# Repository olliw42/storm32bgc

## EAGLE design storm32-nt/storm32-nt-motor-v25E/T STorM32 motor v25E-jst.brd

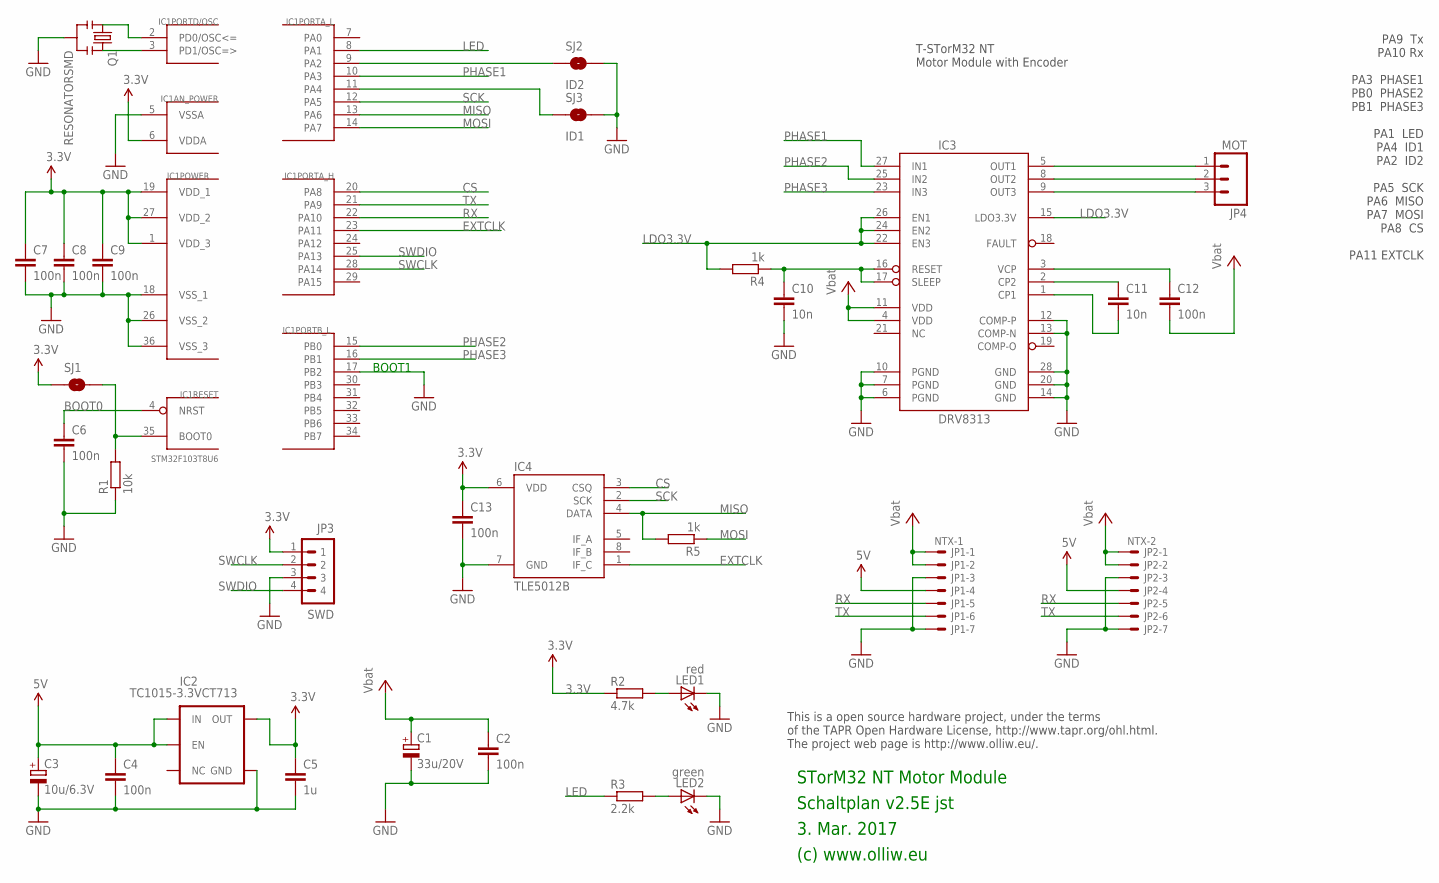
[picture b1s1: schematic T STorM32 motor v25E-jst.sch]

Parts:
C1: 33u/20V; SMC_C
C2, C4, C6, C7, C8, C9, C12, C13: 100n; C0603
C3: 10u/6.3V; SMC_B
C5: 1u; C0603
C10, C11: 10n; C0603
IC1: STM32F103T8U6; VFQFPN36
IC2: TC1015-3.3VCT713; SOT23-5
IC3: DRV8313; HTSSOP28
IC4: TLE5012B; SO08
JP1: NTX-1; SM07B-SRSS-TB
JP2: NTX-2; SM07B-SRSS-TB
JP3: SWD; 4X1_1P27_OCT_BILEX
JP4: MOT; 1X03
LED1: red; CHIPLED_0603
LED2: green; CHIPLED_0603
Q1: RESONATORSMD; RESONATOR-SMD
R1: 10k; R0603
R2: 4.7k; R0603
R3: 2.2k; R0603
R4, R5: 1k; R0603
SJ1: BOOT0; SJ_2S-NO
SJ2: ID2; SJ_2S-NO
SJ3: ID1; SJ_2S-NO

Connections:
3.3V: C5.1, C7.1, C8.1, C9.1, C13.1, IC1.1 (VDD_3), IC1.6 (VDDA), IC1.19 (VDD_1), IC1.27 (VDD_2), IC2.5 (OUT), IC4.6 (VDD), JP3.1, R2.1, SJ1.1
5V: C3.+, C4.1, IC2.1 (IN), IC2.3 (EN), JP1.4, JP2.4
CS: IC1.20 (PA8), IC4.3 (CSQ)
EXTCLK: IC1.23 (PA11), IC4.1 (IF_C)
GND: C1.-, C2.2, C3.-, C4.2, C5.2, C6.2, C7.2, C8.2, C9.2, C10.2, C13.2, IC1.5 (VSSA), IC1.17 (PB2), IC1.18 (VSS_1), IC1.26 (VSS_2), IC1.36 (VSS_3), IC2.2 (GND), IC3.6 (PGND), IC3.7 (PGND), IC3.10 (PGND), IC3.12 (COMP-P), IC3.13 (COMP-N), IC3.14 (GND), IC3.20 (GND), IC3.28 (GND), IC4.7 (GND), JP1.3, JP1.7, JP2.3, JP2.7, JP3.3, LED1.C, LED2.C, Q1.2, R1.1, SJ2.2, SJ3.2
LDO3.3V: IC3.15 (LDO3.3V), IC3.22 (EN3), IC3.24 (EN2), IC3.26 (EN1), R4.2
LED: IC1.8 (PA1), R3.1
MISO: IC1.13 (PA6), IC4.4 (DATA), R5.2
MOSI: IC1.14 (PA7), R5.1
unnamed: IC3.9 (OUT3), JP4.3
unnamed: IC1.9 (PA2), SJ2.1
unnamed: IC1.11 (PA4), SJ3.1
unnamed: C6.1, IC1.4 (NRST)
unnamed: IC1.35 (BOOT0), R1.2, SJ1.2
unnamed: IC1.2 (PD0/OSC<=), Q1.1
unnamed: IC1.3 (PD1/OSC=>), Q1.3
unnamed: LED1.A, R2.2
unnamed: LED2.A, R3.2
unnamed: IC3.8 (OUT2), JP4.2
unnamed: IC3.5 (OUT1), JP4.1
unnamed: C11.1, IC3.2 (CP2)
unnamed: C11.2, IC3.1 (CP1)
unnamed: C10.1, IC3.16 (RESET), IC3.17 (SLEEP), R4.1
unnamed: C12.1, IC3.3 (VCP)
PHASE1: IC1.10 (PA3), IC3.27 (IN1)
PHASE2: IC1.15 (PB0), IC3.25 (IN2)
PHASE3: IC1.16 (PB1), IC3.23 (IN3)
RX: IC1.22 (PA10), JP1.5, JP2.5
SCK: IC1.12 (PA5), IC4.2 (SCK)
SWCLK: IC1.28 (PA14), JP3.2
SWDIO: IC1.25 (PA13), JP3.4
TX: IC1.21 (PA9), JP1.6, JP2.6
VCC: C1.+, C2.1, C12.2, IC3.4 (VDD), IC3.11 (VDD), JP1.1, JP1.2, JP2.1, JP2.2

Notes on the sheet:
3. Mar. 2017
(c) www.olliw.eu
STorM32 NT Motor Module
Schaltplan v2.5E jst
This is a open source hardware project, under the terms of the TAPR Open Hardware License, http://www.tapr.org/ohl.html. The project web page is http://www.olliw.eu/.
T-STorM32 NT Motor Module with Encoder
BOOT1
PA9 Tx PA10 Rx PA3 PHASE1 PB0 PHASE2 PB1 PHASE3 PA1 LED PA4 ID1 PA2 ID2 PA5 SCK PA6 MISO PA7 MOSI PA8 CS PA11 EXTCLK

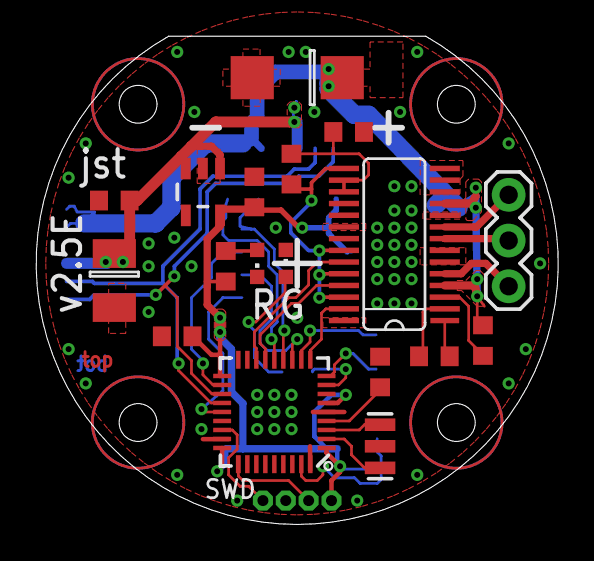
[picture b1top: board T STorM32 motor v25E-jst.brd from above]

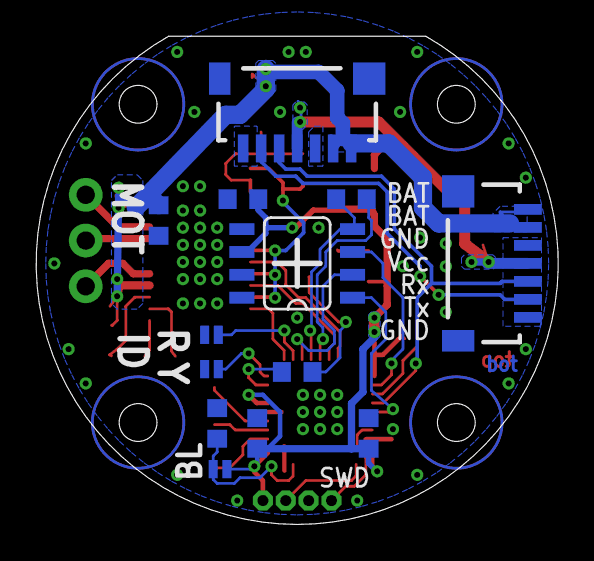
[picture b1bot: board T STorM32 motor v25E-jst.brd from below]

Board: 2 copper layers, 29.0 x 27.1 mm, 32 parts (13 on the bottom side), 33 nets.

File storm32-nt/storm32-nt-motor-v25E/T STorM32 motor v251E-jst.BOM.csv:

"Part";"Value";"Device";"Package";"Description";"";
"C1";"33u/20V";"CPOL-EUSMCC";"SMC_C";"POLARIZED CAPACITOR, European symbol";"";
"C2";"100n";"C-EUC0603";"C0603";"CAPACITOR, European symbol";"";
"C3";"10u/10V";"CPOL-EUSMCB";"SMC_B";"POLARIZED CAPACITOR, European symbol";"";
"C4";"100n";"C-EUC0603";"C0603";"CAPACITOR, European symbol";"";
"C5";"1u";"C-EUC0603";"C0603";"CAPACITOR, European symbol";"";
"C6";"100n";"C-EUC0603";"C0603";"CAPACITOR, European symbol";"";
"C7";"100n";"C-EUC0603";"C0603";"CAPACITOR, European symbol";"";
"C8";"100n";"C-EUC0603";"C0603";"CAPACITOR, European symbol";"";
"C9";"100n";"C-EUC0603";"C0603";"CAPACITOR, European symbol";"";
"C10";"10n";"C-EUC0603";"C0603";"CAPACITOR, European symbol";"";
"C11";"10n";"C-EUC0603";"C0603";"CAPACITOR, European symbol";"";
"C12";"100n";"C-EUC0603";"C0603";"CAPACITOR, European symbol";"";
"C13";"100n";"C-EUC0603";"C0603";"CAPACITOR, European symbol";"";
"IC1";"STM32F103T8";"STM32F10XTXU6";"VFQFPN36";"STM32F101/103 36pad VFQPFN36";"";
"IC2";"TC1015-3.3VCT713";"V_REG_TPS76433SOT23-5";"SOT23-5";"Voltage Regulator";"";
"IC3";"DRV8313PWPR";"DRV8313";"HTSSOP28";"";"";
"IC4";"TLE5012B E1000X";"TLE5012B";"SO08";"";"";
"JP1";"NTX-1";"SM07B-SRSS-TB";"SM07B-SRSS-TB";"Disconnectable Crimp style connector, 1.0mm pitch7 contacts";"";
"JP2";"NTX-2";"SM07B-SRSS-TB";"SM07B-SRSS-TB";"Disconnectable Crimp style connector, 1.0mm pitch7 contacts";"";
"JP3";"SWD";"P4X1_1P27-OCT_BILEX";"4X1_1P27_OCT_BILEX";"";"";
"JP4";"MOT";"M03PTH";"1X03";"Header 3";"";
"LED1";"red";"LEDCHIPLED_0603";"CHIPLED_0603";"LED";"";
"LED2";"green";"LEDCHIPLED_0603";"CHIPLED_0603";"LED";"";
"Q1";"CSTCE8M00G55-R0";"RESONATORSMD";"RESONATOR-SMD";"Resonator";"";
"R1";"10k";"R-EU_R0603";"R0603";"RESISTOR, European symbol";"";
"R2";"4.7k";"R-EU_R0603";"R0603";"RESISTOR, European symbol";"";
"R3";"2.2k";"R-EU_R0603";"R0603";"RESISTOR, European symbol";"";
"R4";"1k";"R-EU_R0603";"R0603";"RESISTOR, European symbol";"";
"R5";"1k";"R-EU_R0603";"R0603";"RESISTOR, European symbol";"";
"SJ1";"BOOT0";"SOLDERJUMPERNO";"SJ_2S-NO";"Solder Jumper";"";
"SJ2";"ID2";"SOLDERJUMPERNO";"SJ_2S-NO";"Solder Jumper";"";
"SJ3";"ID1";"SOLDERJUMPERNO";"SJ_2S-NO";"Solder Jumper";"";

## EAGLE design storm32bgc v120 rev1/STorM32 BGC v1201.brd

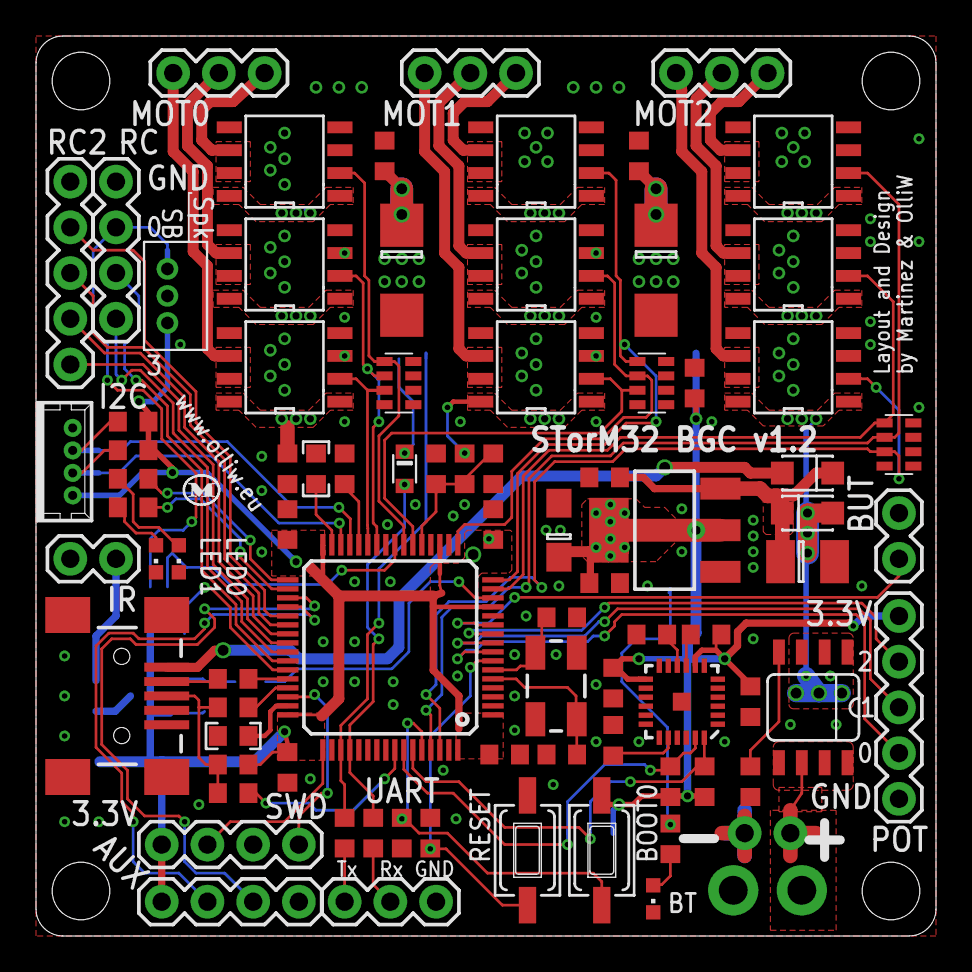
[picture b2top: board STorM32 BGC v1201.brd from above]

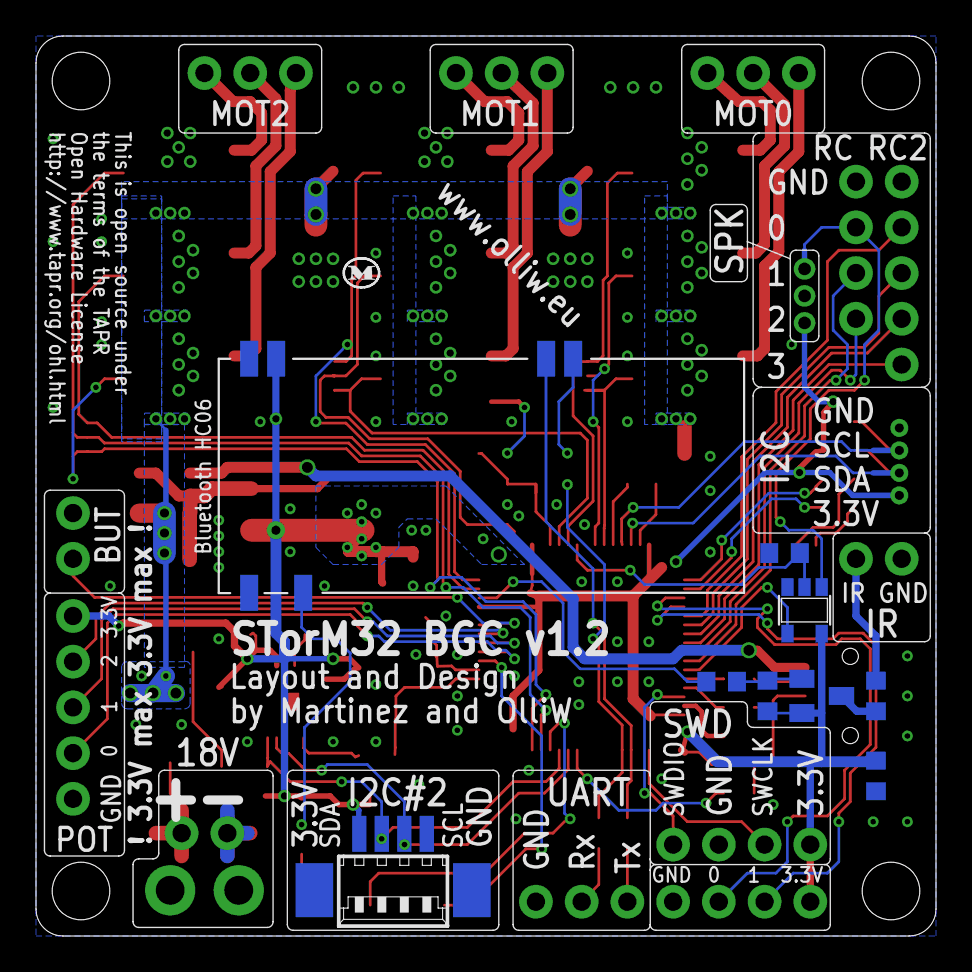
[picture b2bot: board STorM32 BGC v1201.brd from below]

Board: 2 copper layers, 50.0 x 50.0 mm, 93 parts (9 on the bottom side), 77 nets.

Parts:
BAT+: 1X1_WITHOUT
BAT-: 1X1_WITHOUT
C1: 10u/20V; SMC_B
C2, C3, C5, C6, C7, C8, C11, C12, C15, C16, C17, C18, C19, C22, C23: 100n; C0603
C4: 10u/6.3V; SMC_A
C9, C10: 22p; C0603
C13, C14: 33u/20V; SMC_C
C20: 10n; C0603
C21: 2.2n; C0603
D1, D2: PMEG3010ER; SOD123W-DIODE
D3: 1PS76SB40; SOD110-R
IC1: STM32F103RCT6; TQFP64
IC2: NCP1117ST33T3G; SOT223
IC3, IC4, IC5, IC6, IC7, IC8, IC9, IC10, IC11: TC4452DFN08; DFN8
IC12: 74AHC1G86DBV; SOT23-5
IC13: MPU6050; QFN-24
IC14: BT HC06; BT_HC05_BASIC
JP1: USBMINIBSMD; USB-MINIB
JP2: MPU-I2C#1; 53047-04SMALL
JP3: SPK; B3B-ZR
JP4: I2C#2; MOLEX-53261-04-SMD-FLAT
JP5: SWD; 1X04
JP6: UART; 1X03
JP7: RC; 1X04
JP8: POT; 1X05
JP9: RC2; 1X05
JP10: BUT; 1X02
JP11: AUX; 1X04
JP12: MOT0; 1X03
JP13: MOT1; 1X03
JP14: MOT2; 1X03
JP15: IR; 1X02
LED1: green; CHIPLED_0603
LED2: red; CHIPLED_0603
LED3: yellow; CHIPLED_0603
Q1: 7B-8.000MAAJ-T; CRYTSAL-SMD-5X3
R1: 47k; R0603
R2, R3, R16, R17, R20: 10k; R0603
R4, R5: 0; R0603
R6: 1k; R0603
R7, R12, R13, R14, R15, R19, R22, R23, R24, R25: 2.2k; R0603
R8, R9: 22; R0603
R10: 150; R0603
R11, R18: 1.5k; R0603
R21: 47; R0603
RN1, RN2, RN3: 10k; CTS742C083
SW1, SW2: SW_TACT_3X6
T1: SI4835DDY; SO08
T2: BCX71HSMD; SOT23

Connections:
3.3V: C3.1, C4.+, C5.1, C6.1, C7.1, C8.1, C18.1, C19.1, C20.1, C23.1, IC1.1, IC1.13, IC1.19, IC1.32, IC1.48, IC1.64, IC2.2, IC2.4, IC12.5, IC13.8, IC13.13, IC14.12, JP2.1, JP3.1, JP4.1, JP5.4, JP8.5, JP11.4, R11.1, R14.2, R15.2, R20.2, R22.2, R23.2, R24.2, SW2.1, T2.2
A0: IC1.27, IC3.2, RN1.3
A1: IC1.22, IC6.2, RN2.3
A2: IC1.62, IC9.2, RN3.3
AUX0: IC1.35, JP11.2
AUX1: IC1.36, JP11.3
B0: IC1.26, IC4.2, RN1.2
B1: IC1.17, IC7.2, RN2.2
B2: IC1.15, IC10.2, RN3.1
BATP: BAT+.1, T1.5, T1.6, T1.7, T1.8
BOOT1: IC1.28, R3.2
BUT: IC1.11, JP10.2
C0: IC1.23, IC5.2, RN1.1
C1: IC1.16, IC8.2, RN2.1
C2: IC1.61, IC11.2, RN3.2
GND: BAT-.1, C1.-, C2.2, C3.2, C4.-, C5.2, C6.2, C7.2, C8.2, C9.1, C10.1, C11.2, C12.2, C13.-, C14.-, C15.2, C16.2, C17.2, C18.2, C19.2, C20.2, C21.2, C22.2, C23.2, IC1.12, IC1.18, IC1.63, IC2.1, IC3.3, IC3.4, IC3.5, IC4.3, IC4.4, IC4.5, IC5.3, IC5.4, IC5.5, IC6.3, IC6.4, IC6.5, IC7.3, IC7.4, IC7.5, IC8.3, IC8.4, IC8.5, IC9.3, IC9.4, IC9.5, IC10.3, IC10.4, IC10.5, IC11.3, IC11.4, IC11.5, IC12.3, IC13.1, IC13.11, IC13.18, IC14.13, IC14.22, JP1.GND, JP2.4, JP3.2, JP4.4, JP5.2, JP6.1, JP7.1, JP8.1, JP9.1, JP10.1, JP11.1, JP15.1, LED1.C, LED2.C, LED3.C, Q1.2, Q1.4, R1.2, R2.2, R3.1, R4.1, R5.1, R16.1, R18.1, RN1.5, RN1.6, RN1.7, RN1.8, RN2.5, RN2.6, RN2.7, RN2.8, RN3.5, RN3.6, RN3.7, RN3.8, SW1.2
IR: IC1.14, R19.1
LED0: IC1.33, R6.1
LED1: IC1.34, R7.1
LIPO: C12.1, IC1.21, R17.2, R18.2
M0A: IC3.6, IC3.7, JP12.1
M0B: IC4.6, IC4.7, JP12.2
M0C: IC5.6, IC5.7, JP12.3
M1A: IC6.6, IC6.7, JP13.1
M1B: IC7.6, IC7.7, JP13.2
M1C: IC8.6, IC8.7, JP13.3
M2A: IC9.6, IC9.7, JP14.1
M2B: IC10.6, IC10.7, JP14.2
M2C: IC11.6, IC11.7, JP14.3
unnamed: R21.1, T2.3
unnamed: JP15.2, R21.2
unnamed: C11.1, IC1.7, SW1.1
unnamed: IC1.60, R2.1, SW2.2
unnamed: LED1.A, R6.2
unnamed: LED2.A, R7.2
unnamed: IC1.47, R5.2
unnamed: C9.2, IC1.5, Q1.3
unnamed: C10.2, IC1.6, Q1.1
unnamed: JP1.D-, R8.1
unnamed: JP1.D+, R9.1, R10.1, R11.2
unnamed: IC13.9, R22.1
unnamed: C22.1, IC13.10
unnamed: IC14.24, R25.1
unnamed: LED3.A, R25.2
unnamed: R1.1, T1.4
unnamed: C21.1, IC13.20
unnamed: D3.C, IC14.1
unnamed: IC1.31, R4.2
unnamed: R19.2, R20.1, T2.1
unnamed: JP6.2, R13.2
unnamed: JP6.3, R12.2
POT0: IC1.8, JP8.2
POT1: IC1.9, JP8.3
POT2: IC1.10, JP8.4
RC0-IN: IC12.1, JP3.3, JP7.2
RC0/RX: IC1.43, IC12.4
RC1/TX: IC1.42, JP7.3
RC2: IC1.41, JP7.4
RC2-0: IC1.37, JP9.2
RC2-1: IC1.38, JP9.3
RC2-2: IC1.39, JP9.4
RC2-3: IC1.40, JP9.5
RX: D3.A, IC1.52, R13.1
SCL: IC1.29, JP2.3, R14.1
SCL#2: IC1.58, IC13.23, JP4.3, R23.1
SDA: IC1.30, JP2.2, R15.1
SDA#2: IC1.59, IC13.24, JP4.2, R24.1
SWCLK: IC1.49, JP5.3
SWDIO: IC1.46, JP5.1
TX: IC1.51, IC14.2, R12.1
USB-D: IC1.57, R10.2
USB-DM: IC1.44, R8.2
USB-DP: IC1.45, R9.2
VCC: C13.+, C14.+, C15.1, C16.1, C17.1, D1.A, IC3.1, IC3.8, IC4.1, IC4.8, IC5.1, IC5.8, IC6.1, IC6.8, IC7.1, IC7.8, IC8.1, IC8.8, IC9.1, IC9.8, IC10.1, IC10.8, IC11.1, IC11.8, R17.1, T1.1, T1.2, T1.3
VIN: C1.+, C2.1, D1.C, D2.C, IC2.3
VUSB: D2.A, JP1.VBUS
XOR: IC1.24, IC12.2, R16.2

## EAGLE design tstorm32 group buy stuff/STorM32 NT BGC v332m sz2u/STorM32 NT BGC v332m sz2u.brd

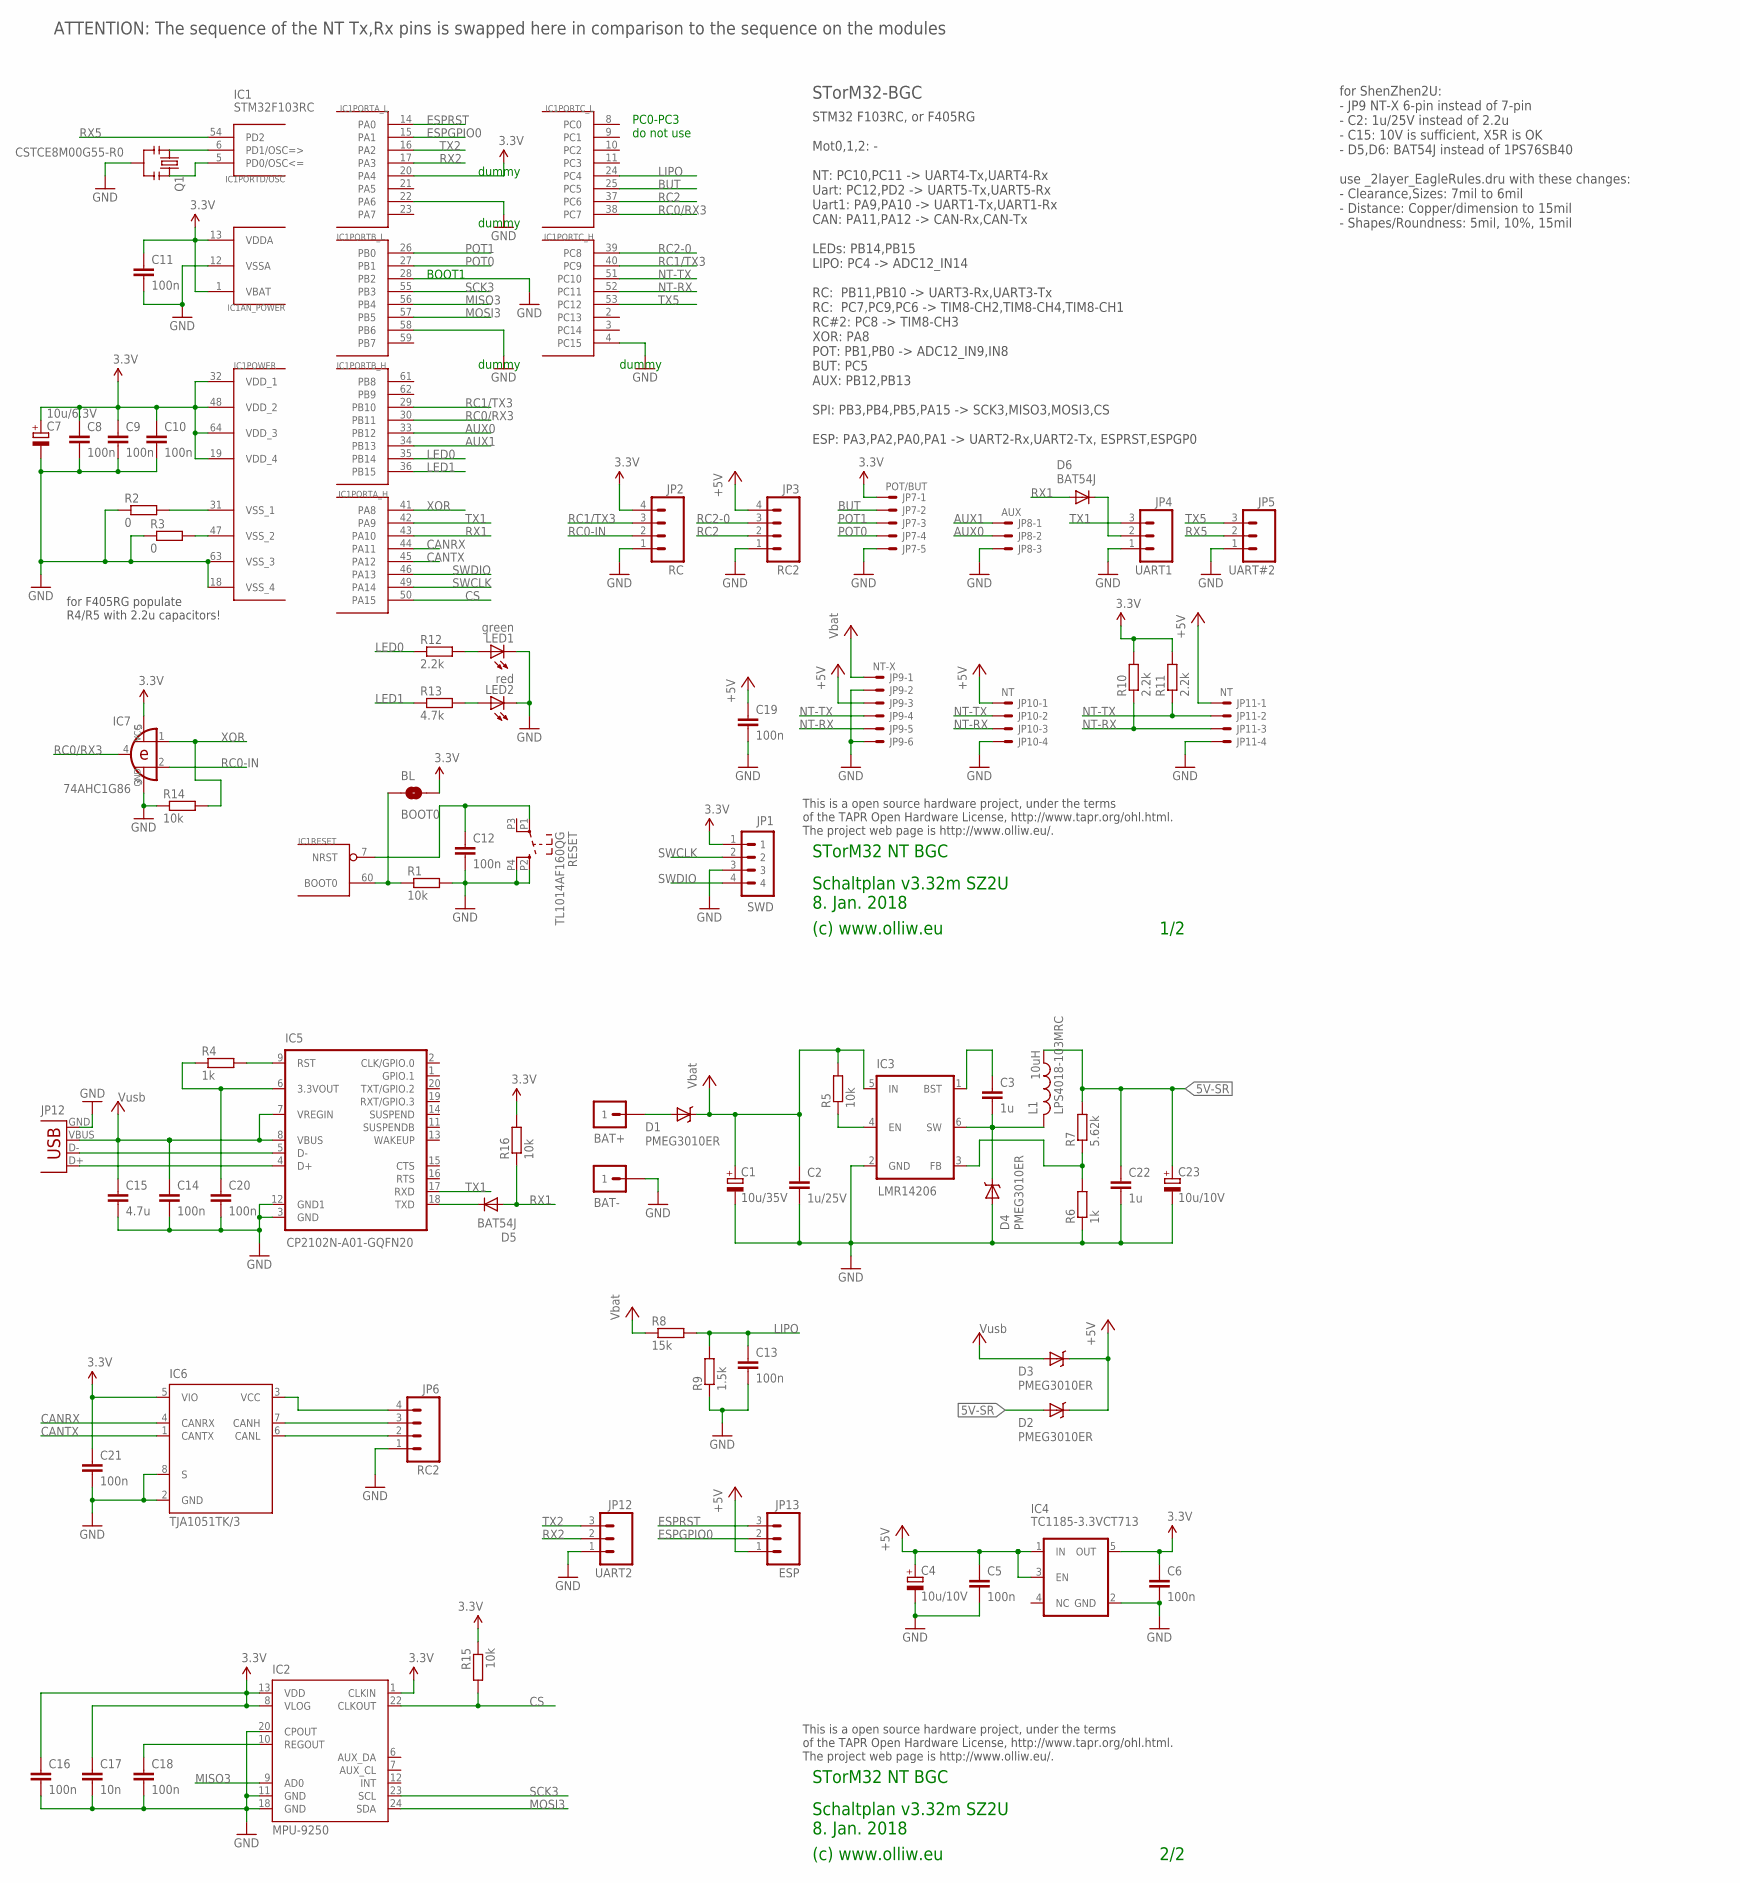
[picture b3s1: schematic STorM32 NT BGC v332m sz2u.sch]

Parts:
BAT+: M1X1; 1X1_WITHOUT
BAT-: M1X1; 1X1_WITHOUT
BL: BOOT0; SJ_2S-NO
C1: 10u/35V; SMC_B
C2: 1u/25V; C0603
C3, C22: 1u; C0603
C4, C23: 10u/10V; SMC_A
C5: 100n; C0603
C6, C8, C9, C10, C11, C12, C13, C14, C16, C18, C19, C20, C21: 100n; C0402
C7: 10u/6.3V; SMC_A
C15: 4.7u; C0603
C17: 10n; C0402
D1, D2, D3, D4: PMEG3010ER; SOD123W-DIODE
D5, D6: BAT54J; SOD110-R
IC1: STM32F103RCT6; TQFP64
IC2: MPU-9250; QFN-24-3X3
IC3: LMR14206; SOT23-6
IC4: TC1185-3.3VCT713; SOT23-5
IC5: CP2102N-A01-GQFN20; QFN20-CP2102N
IC6: TJA1051TK/3; HVSON8
IC7: 74AHC1G86; SOT23-5-VER1
JP1: SWD; 4X1_1P27_OCT_BILEX
JP2: RC; 1X04_NO_SILK
JP3, JP6: RC2; 1X04_NO_SILK
JP4: UART1; 1X03_NO_SILK
JP5: UART#2; 1X03_NO_SILK
JP7: POT/BUT; SM05B-SRSS-TB
JP8: AUX; SM03B-SRSS-TB
JP9: NT-X; SM06B-SRSS-TB
JP10, JP11: NT; SM04B-SRSS-TB
JP12: UART2; 1X03_NO_SILK
JP13: ESP; 1X03_NO_SILK
L1: LPS4018-103MRC; L4X4
LED1: green; CHIPLED_0603
LED2: red; CHIPLED_0603
Q1: CSTCE8M00G55-R0; RESONATOR-SMD
R1, R5, R14, R15, R16: 10k; R0402
R2, R3: 0; R0402
R4, R6: 1k; R0402
R7: 5.62k; R0402
R8: 15k; R0402
R9: 1.5k; R0402
R10, R11, R12: 2.2k; R0402
R13: 4.7k; R0402
RESET: TL1014AF160QG; TACTILE-SWITCH-SMD-RIGHT-TL1014
USB: Amphenol 10118192-0001LF; USB-MICROB

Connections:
3.3V: BL.2, C6.1, C7.+, C8.1, C9.1, C10.1, C11.1, C16.1, C17.1, C21.1, IC1.1 (VBAT), IC1.13 (VDDA), IC1.19 (VDD_4), IC1.20 (PA4), IC1.32 (VDD_1), IC1.48 (VDD_2), IC1.64 (VDD_3), IC2.1 (CLKIN), IC2.8 (VLOG), IC2.13 (VDD), IC4.5 (OUT), IC6.5 (VIO), IC7.5 (VCC), JP1.1, JP2.4, JP7.1, R10.2, R11.2, R15.1, R16.2
3.3V-CP2102: C20.1, IC5.6 (3.3VOUT), R4.1
5V-CAN-RAW: IC6.3 (VCC), JP6.4
5V-SR: C22.1, C23.+, D2.A, L1.1, R7.2
+5V: C4.+, C5.1, C19.1, D2.C, D3.C, IC4.1 (IN), IC4.3 (EN), JP3.4, JP9.3, JP10.1, JP11.1, JP13.1
AUX0: IC1.33 (PB12), JP8.2
AUX1: IC1.34 (PB13), JP8.1
BATP: BAT+.1, D1.A
BOOT0: BL.1, IC1.60 (BOOT0), R1.1
BUT: IC1.25 (PC5), JP7.2
CANH: IC6.7 (CANH), JP6.3
CANL: IC6.6 (CANL), JP6.2
CANRX: IC1.44 (PA11), IC6.4 (CANRX)
CANTX: IC1.45 (PA12), IC6.1 (CANTX)
CS: IC1.50 (PA15), IC2.22 (CLKOUT), R15.2
ESPGPIO0: IC1.15 (PA1), JP13.2
ESPRST: IC1.14 (PA0), JP13.3
GND: BAT-.1, C1.-, C2.2, C4.-, C5.2, C6.2, C7.-, C8.2, C9.2, C10.2, C11.2, C12.2, C13.2, C14.2, C15.2, C16.2, C17.2, C18.2, C19.2, C20.2, C21.2, C22.2, C23.-, D4.A, IC1.4 (PC15), IC1.12 (VSSA), IC1.18 (VSS_4), IC1.22 (PA6), IC1.28 (PB2), IC1.58 (PB6), IC1.63 (VSS_3), IC2.11 (GND), IC2.18 (GND), IC2.20 (CPOUT), IC3.2 (GND), IC4.2 (GND), IC5.3 (GND), IC5.12 (GND1), IC6.2 (GND), IC6.8 (S), IC7.3 (GND), JP1.3, JP2.1, JP3.1, JP4.1, JP5.1, JP6.1, JP7.5, JP8.3, JP9.2, JP9.6, JP10.4, JP11.4, JP12.1, LED1.C, LED2.C, Q1.2, R1.2, R2.1, R3.1, R6.1, R9.1, R14.1, RESET.P2 (1), RESET.P4 (2), USB.GND
LED0: IC1.35 (PB14), R12.1
LED1: IC1.36 (PB15), R13.1
LIPO: C13.1, IC1.24 (PC4), R8.2, R9.2
MISO3: IC1.56 (PB4), IC2.9 (AD0)
MOSI3: IC1.57 (PB5), IC2.24 (SDA)
unnamed: IC5.5 (D-), USB.D-
unnamed: IC5.4 (D+), USB.D+
unnamed: IC3.4 (EN), R5.1
unnamed: LED1.A, R12.2
unnamed: LED2.A, R13.2
unnamed: IC1.47 (VSS_2), R3.2
unnamed: IC1.5 (PD0/OSC<=), Q1.3
unnamed: IC1.6 (PD1/OSC=>), Q1.1
unnamed: C3.1, IC3.1 (BST)
unnamed: IC3.3 (FB), R6.2, R7.1
unnamed: C3.2, D4.C, IC3.6 (SW), L1.2
unnamed: D5.C, IC5.18 (TXD)
unnamed: D6.C, JP4.2
unnamed: IC5.9 (RST), R4.2
unnamed: IC1.31 (VSS_1), R2.2
NRST: C12.1, IC1.7 (NRST), RESET.P1 (3)
NT-RX: IC1.52 (PC11), JP9.5, JP10.3, JP11.3, R10.1
NT-TX: IC1.51 (PC10), JP9.4, JP10.2, JP11.2, R11.1
POT0: IC1.27 (PB1), JP7.4
POT1: IC1.26 (PB0), JP7.3
RC0-IN: IC7.2 (I1), JP2.2
RC0/RX3: IC1.30 (PB11), IC1.38 (PC7), IC7.4 (O)
RC1/TX3: IC1.29 (PB10), IC1.40 (PC9), JP2.3
RC2: IC1.37 (PC6), JP3.2
RC2-0: IC1.39 (PC8), JP3.3
REGOUT: C18.1, IC2.10 (REGOUT)
RX1: D5.A, D6.A, IC1.43 (PA10), R16.1
RX2: IC1.17 (PA3), JP12.2
RX5: IC1.54 (PD2), JP5.2
SCK3: IC1.55 (PB3), IC2.23 (SCL)
SWCLK: IC1.49 (PA14), JP1.2
SWDIO: IC1.46 (PA13), JP1.4
TX1: IC1.42 (PA9), IC5.17 (RXD), JP4.3
TX2: IC1.16 (PA2), JP12.3
TX5: IC1.53 (PC12), JP5.3
VCC: C1.+, C2.1, D1.C, IC3.5 (IN), JP9.1, R5.2, R8.1
VUSB: C14.1, C15.1, D3.A, IC5.7 (VREGIN), IC5.8 (VBUS), USB.VBUS
XOR: IC1.41 (PA8), IC7.1 (I0), R14.2

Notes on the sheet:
(c) www.olliw.eu
STorM32 NT BGC
This is a open source hardware project, under the terms of the TAPR Open Hardware License, http://www.tapr.org/ohl.html. The project web page is http://www.olliw.eu/.
STM32 F103RC, or F405RG Mot0,1,2: - NT: PC10,PC11 -> UART4-Tx,UART4-Rx Uart: PC12,PD2 -> UART5-Tx,UART5-Rx Uart1: PA9,PA10 -> UART1-Tx,UART1-Rx CAN: PA11,PA12 -> CAN-Rx,CAN-Tx LEDs: PB14,PB15 LIPO: PC4 -> ADC12_IN14 RC: PB11,PB10 -> UART3-Rx,UART3-Tx RC: PC7,PC9,PC6 -> TIM8-CH2,TIM8-CH4,TIM8-CH1 RC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
Schaltplan v3.32m SZ2U 8. Jan. 2018
STM32F103RC
STorM32-BGC
for F405RG populate R4/R5 with 2.2u capacitors!
1/2
2/2
IC1
JP12
ATTENTION: The sequence of the NT Tx,Rx pins is swapped here in comparison to the sequence on the modules
BOOT1
dummy
10uH
PC0-PC3 do not use
for ShenZhen2U: - JP9 NT-X 6-pin instead of 7-pin - C2: 1u/25V instead of 2.2u - C15: 10V is sufficient, X5R is OK - D5,D6: BAT54J instead of 1PS76SB40 use _2layer_EagleRules.dru with these changes: - Clearance,Sizes: 7mil to 6mil - Distance: Copper/dimension to 15mil - Shapes/Roundness: 5mil, 10%,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

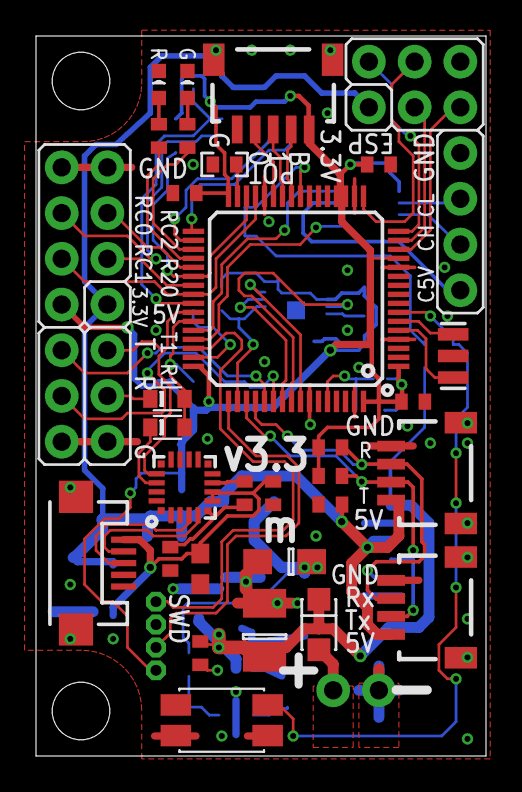
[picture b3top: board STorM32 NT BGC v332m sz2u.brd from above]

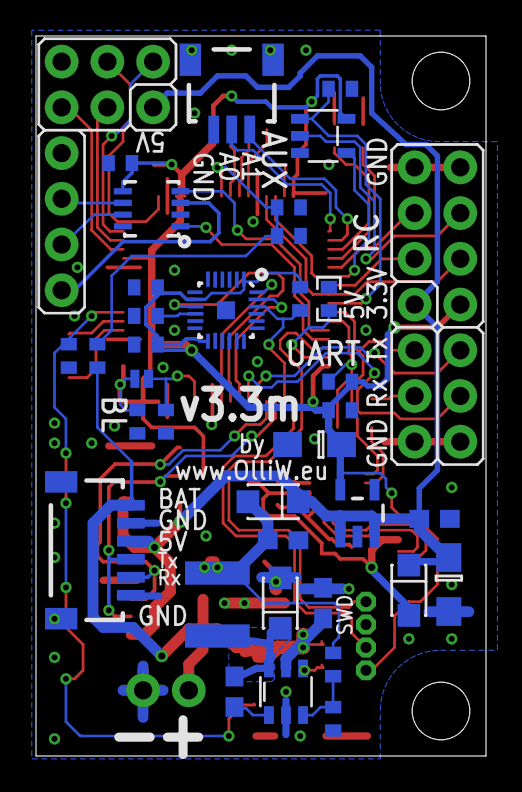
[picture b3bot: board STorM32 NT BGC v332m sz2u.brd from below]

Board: 2 copper layers, 25.0 x 40.0 mm, 74 parts (35 on the bottom side), 61 nets.

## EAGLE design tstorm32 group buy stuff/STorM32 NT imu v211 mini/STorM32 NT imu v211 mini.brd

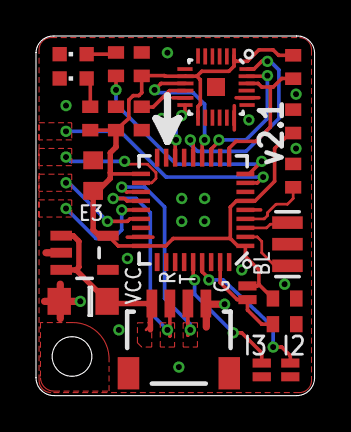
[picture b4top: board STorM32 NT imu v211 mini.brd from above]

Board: 2 copper layers, 15.5 x 20.0 mm, 22 parts (0 on the bottom side), 20 nets.

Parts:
C1: 10u/10V; C0805
C2: 1u; C0603
C3, C4, C5, C6, C8: 100n; C0402
C7: 10n; C0402
IC1: STM32F103T8; VFQFPN36
IC2: TC1015-3.3VCT713; SOT23-5
IC3: MPU9250; QFN-24-3X3
LED1: red; CHIPLED_0603
LED2: green; CHIPLED_0603
NT: NT; SM04B-SRSS-TB
Q1: CSTCE8M00G55-R0; RESONATOR-SMD
R1, R5: 10k; R0402
R2: 4.7k; R0402
R3: 2.2k; R0402
SJ1: BOOT0; SJ_2S-NO
SJ2: IMU-ID2; SJ_2S-NO
SJ3: IMU-ID3; SJ_2S-NO

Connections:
3.3V: C2.1, C4.1, C5.1, C6.1, C7.1, IC1.1, IC1.6, IC1.19, IC1.27, IC2.5, IC3.1, IC3.8, IC3.13, R2.1, R5.2, SJ1.1
5V: C1.1, IC2.1, IC2.3, NT.1
CS: IC1.10, IC3.22, R5.1
GND: C1.2, C2.2, C3.2, C4.2, C5.2, C6.2, C7.2, C8.2, IC1.5, IC1.17, IC1.18, IC1.26, IC1.30, IC1.31, IC1.36, IC2.2, IC3.11, IC3.18, IC3.20, LED1.C, LED2.C, NT.4, Q1.2, R1.1, SJ2.1, SJ3.1
INT: IC1.16, IC3.12
LED: IC1.9, R3.1
unnamed: C3.1, IC1.4
unnamed: LED2.A, R3.2
unnamed: IC1.35, R1.2, SJ1.2
unnamed: IC1.32, SJ3.2
unnamed: IC1.2, Q1.1
unnamed: IC1.3, Q1.3
unnamed: IC1.33, SJ2.2
unnamed: LED1.A, R2.2
unnamed: C8.1, IC3.10
RX: IC1.22, NT.2
SCK: IC1.12, IC3.23
SDI: IC1.14, IC3.24
SDO: IC1.13, IC3.9
TX: IC1.21, NT.3

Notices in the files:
parts and their libraries:
Licensing: CC v3.0 Share-Alike You are welcome to use this library for commercial purposes.
